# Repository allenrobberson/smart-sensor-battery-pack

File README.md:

# Smart Sensor Battery Pack (18350 / 18650 / 21700 / universal)

A small battery board for a Seeed XIAO microcontroller and an SHTC3 temperature and humidity sensor, for building wireless sensors that run on a single lithium-ion cell. The XIAO plugs into sockets on the front, and the cell sits in a holder on the back.

This is a fork of [FeatureNAB/smart-sensor-battery-pack](https://github.com/FeatureNAB/smart-sensor-battery-pack). It adds two larger battery sizes (18650 and 21700), a **universal board** that takes any of the three holders, a few protection and power improvements, and ready-to-use ESPHome firmware for Home Assistant. All the boards share the same circuit and front-side layout. The full list of changes is under [Changes from the original design](#changes-from-the-original-design).

**Downloads:** each board option (18350, 18650, 21700, universal) comes as one zip on the [Releases page](https://github.com/allenrobberson/smart-sensor-battery-pack/releases). Each zip has the Gerbers, the JLCPCB BOM and placement files, the case STLs, the firmware and a KiCad project that opens on its own.

> **U6 rotation fix (12 November 2026):** placement (CPL) files downloaded before this date have U6 (CSD85301Q2) at 180°; the correct angle is 90°. Use the v1.0 release files. If you already ordered with the old files, ask JLCPCB to rotate U6 to 90° (see [the rotation note](#assembled-by-jlcpcb-bom-and-placement-files)).

The original design, with the build, design theory and assembly, is explained in this video:

## Thank you
A big thank you to **FeatureNAB** for designing this board and sharing it openly, along with the video that explains how and why it works. The charging, protection and sensor-isolation design, the compact layout, and the KiCad project are all their work. This fork only builds on that foundation. If you find this useful, please watch and support the [original video](https://www.youtube.com/watch?v=-wEKOhVZ0NM) and [repository](https://github.com/FeatureNAB/smart-sensor-battery-pack).

## Changes from the original design
**New board sizes**
- **18650 board** (`variants/18650/`): Keystone 1042 holder, 23 x 86.25 mm.
- **21700 board** (`variants/21700/`): Keystone 1121 holder (also fits 20700), 24 x 84.55 mm.
- **Universal board** (`variants/universal/`): one 24 x 86.25 mm board with pads and peg holes for the 1096, 1042 *or* 1121 holder, so one design covers 18350, 18650 and 21700. See [Universal](#universal-18350-18650-and-21700-on-one-board).
- **3D-printable case** (`case/`): a base and lid for every board size, including the universal board, with a USB-C window, sensor vents and wall-mount tabs. See [3D-printable case](#3d-printable-case).
- **Variant generator** (`tools/make_variant.py`): rebuilds the larger boards from the 18350 master after any change, swaps the holder, resizes the outline and checks that the holder's holes clear existing copper.

**Circuit changes (all boards)**

| Part | Original | This fork | Why |
|------|----------|-----------|-----|
| Q2 (new) | — | AO3401A P-MOSFET in the battery + line | Protects everything if the cell is inserted backwards |
| U4 regulator | TPS7A05 (200 mA) | RT9080-33GJ5 (600 mA, 2 µA quiescent) | The ESP32-C6 draws up to 354 mA when Wi-Fi transmits; same footprint and pinout |
| C3 (3.3 V cap) | 2.2 µF | 10 µF | Absorbs Wi-Fi current bursts |
| R2 (charger TS) | 10 kΩ fixed resistor | 10 kΩ NTC thermistor, moved away from the charger | Stops charging when too cold or hot; the fixed resistor disabled this |
| R1 (charge current) | 1.2 kΩ (450 mA) | 18350: unchanged. 18650 and 21700: 910 Ω (about 590 mA). Universal: 1 kΩ (about 540 mA) | Larger cells finish charging inside the charger's 10-hour safety timer |
| U1 (schematic) | XIAO nRF52840 | XIAO ESP32-C6 | Matches the firmware; the sockets are the same |

The 18350 board keeps its original size and front layout; Q2 and the moved thermistor fit in free space in the top-right corner.

**Firmware and Home Assistant (new)**
- **ESPHome config** for the XIAO ESP32-C6 (`firmware/`) with deep sleep, sensor power sequencing, internal I2C pull-ups disabled and pins released before sleep, so the sensor is never powered through its data lines.
- **Home Assistant package** (`homeassistant/`) adding a "stay awake" toggle for over-the-air updates, plus a secrets template.

**Manufacturing files (new)**
- **Gerber zips** for all four boards (18350, 18650, 21700, universal) in `gerbers/`, generated by `tools/make_gerbers.py` and checked for shorts and broken connections.
- **JLCPCB assembly files** (BOM with LCSC part numbers, and placement files) in `assembly/`; the schematics now carry LCSC numbers for the new parts.

**Documentation**
- **I2C note corrected:** the original note said pull-ups were missing. R9 and R10 are already in the design, on the switched sensor rail.
- **Points from the original project's [issue #1](https://github.com/FeatureNAB/smart-sensor-battery-pack/issues/1) ("Missing Pull Up Resistor"):**
  - *Pull-ups on the switched rail (3V_SW) vs. 3V3:* kept on 3V_SW on purpose. Pull-ups on the always-on 3V3 would push current into the SHTC3 through SDA/SCL while its supply is off (phantom powering). On 3V_SW, the pull-ups and the sensor are switched on and off together.
  - *"The sensor has to be powered before the bus starts":* the firmware switches the sensor rail on at boot priority 1200, before I2C sets up (priority 1000), and waits 5 ms so the sensors are ready. No extra YAML is needed.
  - *"Use the internal pull-ups instead":* not used. The ESP32-C6's internal pull-ups are about 45 kΩ, too weak to be reliable, and they would phantom-power the sensor during sleep. They are disabled.
  - *Pull-up current:* none while the bus is idle (I2C is open-drain), and none at all while the rail is off.
  - *Measured 380 µA asleep and a 3.45 s wake:* the firmware now sleeps 2 s after Home Assistant connects instead of staying awake a fixed 20 s, so a typical wake is about 3–6 s and uses roughly a quarter of the energy. See [Sleep current](#sleep-current) for how to measure.
  - *Static IP slower for one tester:* the config now says to measure before relying on a static IP.
  - *Edge.Cuts DRC errors:* the outlines of all three boards here are closed (checked: no open ends).
  - *Larger + / − battery marks:* the holder footprints have small + and − marks on the back silkscreen. Reverse-battery protection (Q2) also protects the board if a cell goes in backwards.
- **README rewritten:** board descriptions, comparison images, setup steps and known limitations.

## Quick start
Here's everything you need to build one, in order:

1. **Pick a board:** 18350 (smallest), 18650 or 21700 (longest runtime), or the universal board if you want to choose the cell later. See [The board designs](#the-board-designs).
2. **Order the board:** upload that board's Gerber zip from [`gerbers/`](gerbers) to JLCPCB. Optionally add assembly with the matching BOM and placement files from [`assembly/`](assembly); see [Ordering boards](#ordering-boards-gerber-files).
3. **Buy the parts that aren't on the board order:**
   - The **battery holder** for your size, from DigiKey (see [Battery holders](#battery-holders)).
   - A **Seeed XIAO ESP32-C6** ([product wiki](https://wiki.seeedstudio.com/xiao_esp32c6_getting_started)).
   - A **lithium-ion cell** (see [Batteries](#batteries)).
4. **Solder the holder, then check the board** before inserting a cell (see [Assembly and first power-up](#assembly-and-first-power-up)).
5. **Flash the firmware and add the sensor to Home Assistant** (see [Firmware](#firmware-esphome-xiao-esp32-c6)).
6. **Optionally plug in a second sensor** (see [Adding other sensors](#adding-other-sensors)).

## What the board does
- **Microcontroller:** made for a Seeed **XIAO ESP32-C6**. The board uses D2 (GPIO2) for battery voltage, D4/D5 (GPIO22/23) for I2C and D10 (GPIO18) to switch the sensor power.
- **Charging:** a BQ21040 charges the cell from the XIAO's USB 5 V, and an LED shows charge status. R1 sets the charge current: 450 mA on the 18350 board and about 590 mA on the 18650 and 21700 boards, so a full charge fits inside the charger's 10-hour safety timer.
- **Battery temperature:** a 10 kΩ NTC thermistor (R2, Murata NCP15XH103F03RC) on the charger's TS pin stops charging when the board is too cold or too hot for lithium-ion. It sits in the corner furthest from the charger so the charger's own heat doesn't trip it.
- **Reverse-battery protection:** a P-channel MOSFET (Q2, AO3401A) in series with the cell's + terminal, with its gate on the cell's − terminal. A correctly inserted cell turns it fully on in both directions, for charging and discharging. A reversed cell leaves it off, and its body diode blocks the current.
- **Cell protection:** a BQ29700 protector with a CSD85301Q2 dual MOSFET guards against over-charge, over-discharge and over-current.
- **Power:** an RT9080-33GJ5 regulator (600 mA, 2 µA quiescent current) supplies 3.3 V to the XIAO. That covers the ESP32-C6's Wi-Fi transmit peaks (up to 354 mA at full power) with headroom, and a 10 µF capacitor (C3) on 3.3 V absorbs the bursts.
- **Battery monitoring:** a 5.1 MΩ / 5.1 MΩ divider brings the battery voltage to a XIAO analog pin (BATT_SENSE) and draws about 0.4 µA.
- **Switched sensor power:** a P-channel MOSFET (Q1, AO3401A) lets the XIAO turn the sensor rail (3V_SW) off between readings. The I2C pull-ups (R9, R10) are on that rail too, so nothing on the sensor side draws current while the XIAO sleeps.
- **Sensor:** an SHTC3 sits on a slotted tab at the bottom edge, thermally isolated from the rest of the board, with an extra socket for a plug-in I2C sensor.

## The board designs
All the boards share the same schematic and the same front-side parts and routing. Only the holder on the back, the board outline and the two battery traces change. The extra length is added at the BAT+ end, so the sensor tab stays where it is.

| Cell | Holder (back side) | Holder mounting | Board size | KiCad project |
|------|--------------------|-----------------|------------|---------------|
| 18350 | Keystone 1096 | Surface mount | 23 x 56 mm | repository root (original design) |
| 18650 | Keystone 1042 | Surface mount | 23 x 86.25 mm | `variants/18650/` |
| 21700 | Keystone 1121 (fits 20700 and 21700) | Through-hole solder lugs | 24 x 84.55 mm | `variants/21700/` |
| **Universal** | Keystone 1096, 1042 **or** 1121 | SMD pads + lug holes for all three | 24 x 86.25 mm | `variants/universal/` |

### 18350
The original, most compact design. The Keystone 1096 holder covers the whole back of the board.

### 18650
The same board stretched to 86.25 mm for a Keystone 1042 holder. The holder's locating holes are placed to clear all existing copper. The BAT- pad overhangs the bottom edge by 0.25 mm, which DRC will flag; the original board overhangs its BAT+ pad by 0.95 mm in the same way.

### 21700
Uses a Keystone 1121 holder. The holder is 23.06 mm wide, so the board is 1 mm wider than the original, with the extra width on the right so the sensor tab is unchanged. The holder's solder lugs go through the board and are soldered from the front.

The footprint was drawn from Keystone drawing 1121 rev A. The lug holes are drilled 1.7 mm instead of the drawing's 1.32 mm, because the drawing gives the lug pin itself as 1.57 mm. Check a lug against the hole before ordering.

### Universal (18350, 18650 and 21700 on one board)
One board that takes any of the three holders, so you can order a single design and choose the cell later. It is the 21700 board lengthened to 86.25 mm (the 1042's length), 24 mm wide.

- **BAT- end (bottom):** one larger SMD pad covers both the 1096 and the 1042 contact, with the 1121's plated lug hole in the middle of it. All three holders' − contacts land here.
- **BAT+ end (top):** the + pad for the 1042 (18650) sits at the top edge, with the 1121's (21700) lug hole inside it. A second + pad for the 1096 (18350) sits 30.7 mm further down. The two are joined by the BAT+ trace on the back, under solder mask, so there is no long strip of bare battery copper. The back silkscreen shows which + pad belongs to which cell (`18650 21700` and `18350`), plus large + and − marks.
- **Locating holes:** every holder's pegs have a hole. Where two holders' pegs overlap, the holes are merged into slots: one small and one large slot on the left, and one large slot on the right. All holes keep at least 0.3 mm from copper.
- **Charge current:** R1 is **1 kΩ (about 540 mA)**, LCSC C11702, a basic part. That's under 0.5C for a 1100 mAh 18350 and still charges a 4500 mAh 21700 inside the charger's 10-hour safety timer. With a 5000 mAh cell charged from empty, the timer can stop the charge just before it finishes; unplugging and replugging USB restarts it. For an 18650/21700-only build, you can fit 910 Ω (C44933) instead.
- **Soldering the holder:** for the 1096 or 1042, solder the contacts to the pads; the small lug holes under them just fill with solder. For the 1121, solder its lugs from the front as on the 21700 board. Only fit one holder.

The front side, parts and routing are the same as the other three boards, so the same firmware and BOM apply. The only BOM difference is R1. The board and its files were made by `tools/make_universal.py`.

**What has been checked:** the Gerbers have no shorts or broken nets; every hole and slot keeps at least 0.3 mm from other-net copper; no copper is within 0.25 mm of the board edge; JLCPCB accepted the files, matched all 19 parts and showed the slots correctly; and every part's rotation was checked in JLCPCB's placement preview (pin-1 marks and leads on pads). **Not yet checked:** a KiCad DRC run (open `variants/universal/` in KiCad, press B to refill zones, then run DRC) and a physical test-fit of each holder. Check the peg slots against a real holder before ordering in quantity.

## 3D-printable case
A two-part case (base + lid) for every board, in [`case/stl/`](case/stl). Details and print settings are in [`case/README.md`](case/README.md).

| Board | Print |
|---|---|
| 18350 | [`case-18350-base.stl`](case/stl/case-18350-base.stl) + [`case-18350-lid.stl`](case/stl/case-18350-lid.stl) |
| 18650 | [`case-18650-base.stl`](case/stl/case-18650-base.stl) + [`case-18650-lid.stl`](case/stl/case-18650-lid.stl) |
| 21700 | [`case-21700-base.stl`](case/stl/case-21700-base.stl) + [`case-21700-lid.stl`](case/stl/case-21700-lid.stl) |
| Universal | the base for the holder you fitted ([`18350`](case/stl/case-universal-18350-base.stl), [`18650`](case/stl/case-universal-18650-base.stl) or [`21700`](case/stl/case-universal-21700-base.stl)) + [`case-universal-lid.stl`](case/stl/case-universal-lid.stl) |

More views of each case (exploded, base, lid from below, assembled) and cut-away fit checks are in [`case/images/`](case/images).

- **Base:** the board drops in battery-side down and rests on ribs under the holder's end walls.
- **Lid:** clicks onto a lip on the base; small fingers stop just above the board's edges so it can't move.
- **USB-C window:** lined up with the XIAO's USB-C port, so you can charge and flash without opening the case.
- **Vents** next to the SHTC3 sensor tab and across the roof, so the sensor reads room air; **wall-mount tabs** on both ends.
- **Checked:** the generator checks every case against the board, holder, cell, every part, the XIAO and the USB-C plug path, and checks that the STLs are watertight. The case hasn't been test-printed yet. If your sockets or headers are a different height, change the values at the top of [`tools/make_case.py`](tools/make_case.py) and run it again.

## Ordering boards (Gerber files)
Ready-to-upload Gerber zips for all four boards are in [`gerbers/`](gerbers):

| Board | File | Size |
|-------|------|------|
| 18350 | [`gerbers/SSB-18350-gerbers.zip`](gerbers/SSB-18350-gerbers.zip) | 23 x 56 mm |
| 18650 | [`gerbers/SSB-18650-gerbers.zip`](gerbers/SSB-18650-gerbers.zip) | 23 x 86.25 mm |
| 21700 | [`gerbers/SSB-21700-gerbers.zip`](gerbers/SSB-21700-gerbers.zip) | 24 x 84.55 mm |
| Universal | [`gerbers/SSB-UNIVERSAL-gerbers.zip`](gerbers/SSB-UNIVERSAL-gerbers.zip) | 24 x 86.25 mm |

**To order at JLCPCB:** upload a zip on the quote page and keep the defaults: 2 layers, 1.6 mm FR-4, 1 oz copper. Choose any solder-mask colour. If you want JLCPCB to assemble the parts, pick **LeadFree HASL** so the cheaper Economic assembly is allowed (see [Tested JLCPCB order settings](#tested-jlcpcb-order-settings-november-2026)). Each zip holds both copper layers, solder mask, paste, silkscreen, the board outline, and plated and non-plated drill files.

*Copper as written to the Gerbers (white = copper), front and back for 18350, 18650 and 21700. The back views are mirrored as if the board were flipped over.*

### Assembled by JLCPCB (BOM and placement files)
To have JLCPCB solder the parts, choose **PCB Assembly** (top side) on the quote page, then upload the BOM and placement (CPL) files for the same board from [`assembly/`](assembly):

| Board | BOM | Placement |
|-------|-----|-----------|
| 18350 | [`SSB-18350-BOM.csv`](assembly/SSB-18350-BOM.csv) | [`SSB-18350-CPL.csv`](assembly/SSB-18350-CPL.csv) |
| 18650 | [`SSB-18650-BOM.csv`](assembly/SSB-18650-BOM.csv) | [`SSB-18650-CPL.csv`](assembly/SSB-18650-CPL.csv) |
| 21700 | [`SSB-21700-BOM.csv`](assembly/SSB-21700-BOM.csv) | [`SSB-21700-CPL.csv`](assembly/SSB-21700-CPL.csv) |
| Universal | [`SSB-UNIVERSAL-BOM.csv`](assembly/SSB-UNIVERSAL-BOM.csv) | [`SSB-UNIVERSAL-CPL.csv`](assembly/SSB-UNIVERSAL-CPL.csv) |

Every part except the battery holder uses a JLCPCB/LCSC part number:

| Part | Designator | LCSC # |
|------|-----------|--------|
| Charger BQ21040DBVR | U2 | C202311 |
| Protector BQ29700DSER | U5 | C183096 |
| Dual MOSFET CSD85301Q2 | U6 | C544396 |
| Regulator RT9080-33GJ5 | U4 | C841192 |
| P-MOSFET AO3401A | Q1, Q2 | C15127 |
| SHTC3 sensor | U7 | C194656 |
| 10 kΩ NTC (Murata NCP15XH103F03RC) | R2 | C77131 |
| 10 µF 0603 | C3 | C19702 (basic part) |
| 2.2 µF 0603 | C1, C2 | C23630 (basic part) |
| 100 nF 0402 | C4, C5, C6 | C1525 |
| Charge-current resistor | R1 | 1.2 kΩ C25862 (18350), 910 Ω C44933 (18650, 21700) |
| Other 0402 resistors, LED | R3–R12, D1 | see the BOM files |
| XIAO sockets 1x7 / 1x5 SMD | J1, J2, J3 / J5 | C42379199 / C42379198 |

Things to know before ordering assembly:
- **Battery holder:** BT1 is not in the BOM, so buy it separately and solder it yourself (see [Battery holders](#battery-holders) below).
- **Extended parts:** most of the ICs are JLCPCB "extended" parts, which carry a small one-time loading fee each. Stock changes, so the quote page will flag anything that has run out.
- **Rotations are already corrected:** the CPL files include JLCPCB's zero-angle offsets for the sockets, SOT-23, SOT-23-5, SOT-23-6, SHTC3 and CSD85301Q2 parts (see `ROTATION_FIX` in `tools/make_jlc_bom.py`). Every part was checked in JLCPCB's placement preview: each IC's pin-1 marker sits at the board's pin-1 mark and its leads on the pads. All four boards share identical front-side pads and placement data, so the check covers all of them. **U6 (CSD85301Q2) needs 90°, not 180°:** JLCPCB's library footprint for C544396 has the pins in rows with pin 1 bottom-left, while the KiCad footprint has them in columns. The first CPL files (used for the November 2026 order of the 18350/18650/21700 boards) had U6 at 180°, which turns the part 90° on its pads. This was fixed on 12 November 2026; if you downloaded the assembly files before then, download them again. **If you already placed an order with the old CPL file,** message JLCPCB (through the order's File Review or support chat) before assembly and ask them to place U6 (CSD85301Q2, C544396) at 90° so that pin 1 sits at the silkscreen dot. They can correct the rotation on an order that is still in review.
- **The XIAO:** it plugs into the sockets and isn't part of the order.

#### Tested JLCPCB order settings (November 2026)
The 18350, 18650 and 21700 Gerbers and BOMs are exactly the ones uploaded for a real order of those three boards. Their CPL (placement) files have since had one fix: U6 is now at 90° instead of 180° (see the rotation note above). The universal board's files were uploaded with the same settings and quoted at **$73.82** for 5 assembled boards ($5.10 PCB + $68.72 assembly, including $0.91 nitrogen reflow); all 19 parts matched and were in stock, and JLCPCB's preview showed its slotted holes correctly. These settings went through without errors:

| Setting | Value | Why |
|---------|-------|-----|
| Surface finish | **LeadFree HASL** | Economic PCBA does not accept OSP. Lead-free HASL costs about $1.10 more, but it unlocks the much cheaper assembly tier |
| PCBA type | **Economic** | Setup fee about $8 instead of about $26, a $1.55 stencil instead of $8.27, and no per-feeder loading fees (only a ~$3 fee per extended part) |
| PCB qty / PCBA qty | 5 / 5 | Economic PCBA allows 2 to 50 assembled boards |
| Assembly side | Top | BT1 on the back is soldered by hand |
| Tooling holes | Added by JLCPCB | Default |
| Product description | Sensor\Controller\Precision Instrument / Temperature Sensor | Needed for customs |
| Assembly remark | (optional) "Please confirm pin 1 of U6 (CSD85301Q2, C544396) is at the silkscreen dot, bottom-right of U6." | A second check on the one part whose rotation had to be corrected. The **Assembly Remark** box doesn't always appear; if it's missing, raise it during **File Review** in your order history. Don't use the 200-character **PCB Remark** box, which goes to the board factory, not assembly. |

Quoted price for 5 assembled boards, before shipping and coupons:

| Board | PCB | Assembly (Economic) | Total |
|-------|-----|---------------------|-------|
| 18350 | $5.10 | $68.74 | **$73.84** |
| 18650 | $5.10 | $71.84 | **$76.94** |
| 21700 | $5.10 | $71.84 | **$76.94** |

Assembly breakdown (Economic PCBA, 5 boards):

| Item | 18350 | 18650 | 21700 |
|------|-------|-------|-------|
| Setup fee | $8.24 | $8.24 | $8.24 |
| Stencil | $1.55 | $1.55 | $1.55 |
| Components (19 BOM lines) | $26.09 | $26.10 | $26.10 |
| Extended components fee | $30.90 | $33.99 | $33.99 |
| SMT assembly | $1.05 | $1.05 | $1.05 |
| Nitrogen reflow | $0.91 | $0.91 | $0.91 |
| **Assembly total** | **$68.74** | **$71.84** | **$71.84** |
| PCB (5 boards, lead-free HASL) | $5.10 | $5.10 | $5.10 |
| **Per order** | **$73.84** | **$76.94** | **$76.94** |
| **Per assembled board** | **$14.77** | **$15.39** | **$15.39** |

Universal board (quoted the same way): $5.10 PCB + $68.72 assembly = **$73.82** for 5 assembled boards ($14.76 each), the same extended-part fees as the 18350.

The 18350 has one fewer extended part than the other two (its R1, C25862, is a basic part), so its fee is lower.

All three boards in one checkout (15 assembled boards), as actually ordered and shipped to the US in November 2026:

| | Cost |
|---|---|
| Merchandise (3 × PCB + PCBA) | $227.72 |
| Shipping (the cart page had estimated $31.69 for UPS Express Saver) | $64.13 |
| US customs duties and taxes | $79.73 |
| Duty and tax disbursement fee | $4.44 |
| **Order total** | **$376.02** (about $25 per assembled board) |

**Budget for more than the cart shows.** The cart's shipping estimate is only a starting point: the shipping charge depends on the method you choose at checkout. US import duties and taxes on the assembled boards came to about 35% of the merchandise total, and JLCPCB charges them at checkout (DDP). Coupons (below) come off the total. Ordering fewer board sizes lowers every line, since each design is a separate PCB + PCBA order.

Not included: the battery holder (BT1, bought separately, see [Battery holders](#battery-holders)), the XIAO ESP32-C6 and the battery.

**Coupons:** JLCPCB uses account coupons rather than codes, and you choose them in the payment step of checkout. New accounts get New User SMT ($10), PCB ($6) and Shipping ($10) coupons, and the [coupon center](https://jlcpcb.com/coupon-center) has more (for example, "PCBA Special Offer" $9/$6). Checking out in the **JLCONE desktop app** unlocks a "JLCONE PCBA $20" coupon for assembly orders over $100, which beats the $10 one for a three-board order. JLCPCB's terms allow one coupon per order, so the checkout page has the final say. Check out all three boards together: separate orders each pay their own shipping (about $27), which costs more than the extra coupons save.

For comparison, the same 18350 order as *Standard* PCBA on OSP came to $96.33.

**Ways to cut the cost further:**
- **Order 2 assembled boards instead of 5.** Most of the assembly cost is per-order fees (setup, extended-part fees), so 2 boards cost only a little less than 5, but the total is still lower if you only need one or two.
- **Order one or two sizes, not all three.** Each design pays its own setup and extended-part fees.
- **Solder the XIAO sockets yourself.** J1–J3 and J5 (C42379199, C42379198) cost about $5.65 in parts per 5-board order, plus two extended-part fees (about $6). Untick them on the BOM page and solder ordinary 2.54 mm female headers.
- **Drop the status LED.** D1 (and its resistor R8) are optional. Unticking D1 saves one extended-part fee.
- **Basic parts were preferred** where they did not change the circuit: R7 (100 kΩ) uses basic part C25741.
- **Order only the universal board** if you haven't decided on a cell size: one design covers all three holders, so you pay one set of setup and extended-part fees.

**Part changes made while ordering:**
- **R1 on the 18650/21700:** C4129882 (910 Ω, 5%) was out of stock, so R1 is now Uniroyal 0402WGF9100TCE, **C44933** (910 Ω, 1%, about 228k in stock). The value and charge current (about 590 mA) are unchanged.
- **R7, all boards:** now C25741 (basic, 1%) instead of C25530 (extended, 5%). Same 100 kΩ value.

### Battery holders
**Note:** the battery holder is the one part JLCPCB does not assemble. It isn't in the BOM, because JLCPCB doesn't reliably stock these Keystone holders and they mount on the back of the board, which would need a second, more expensive assembly side. Order the holder for your board size and solder it yourself after the boards arrive.

Each board is laid out for one specific Keystone holder, and only that part fits its pads and locating holes:

| Board | Holder | Mounting | DigiKey |
|-------|--------|----------|-----|
| 18350 | Keystone **1096** | Surface mount (tabs soldered on the back) | [36-1096-ND](https://www.digikey.com/en/products/detail/keystone-electronics/1096/5057788) |
| 18650 | Keystone **1042** | Surface mount (tabs soldered on the back) | [36-1042-ND](https://www.digikey.com/en/products/detail/keystone-electronics/1042/2745668) |
| 21700 | Keystone **1121** (fits 20700 and 21700) | Through-hole lugs (soldered from the front) | [36-1121-ND](https://www.digikey.com/en/products/detail/keystone-electronics/1121/12751670) |

**Soldering tips**
- **1096 and 1042:** the holder sits on the back. Tack one tab, check the holder is flat with its locating pegs in the holes, then solder the other tab. The tabs are large, so use a hot iron (about 350 °C) and plenty of flux.
- **1121:** push the lugs and pegs through from the back, then solder the two lugs on the front.
- **Polarity:** check it before inserting a cell. The + end of the holder must match the + mark on the board (the BAT+ end, away from the sensor tab). Q2 protects the board if a cell goes in backwards, but double-check anyway.

The files come from [`tools/make_jlc_bom.py`](tools/make_jlc_bom.py), which reads the *LCSC Part no.* field from each schematic and the positions from the board, in the same coordinates as the Gerbers.

**How these were made:** KiCad was not available, so the files were generated by [`tools/make_gerbers.py`](tools/make_gerbers.py) directly from the `.kicad_pcb` files. It fills the copper pours itself: ground copper everywhere, a 0.5 mm gap around every other net and the board edge, and no copper in the keep-out areas. Every copper layer was then rasterized at 0.02 mm and checked automatically. There are no shorts between nets, no broken connections, and every pad, via and trace sits on copper. The check was itself tested by deliberately breaking a trace, which it caught. The differences from a KiCad export are:
- **Solid ground connections:** pads and vias on the ground pour are joined solidly rather than through thermal-relief spokes. Ground pads take a little longer to heat when hand-soldering.
- **Square pad corners:** rounded-rectangle pads are drawn as plain rectangles.
- **Outline-only silkscreen:** part outlines are drawn, but there's no text (reference designators and the logo). Use the board images above while assembling.

If you have KiCad 9, the safer route is still to open each project, press **B** to refill the zones, run DRC, and plot your own Gerbers. To regenerate these files after a design change, run:
```
python3 tools/make_gerbers.py <board.kicad_pcb> <output_dir> --name <prefix>
```

## Before ordering boards
The design changes in this fork (reverse-battery transistor, NTC, new regulator, larger boards) were made by script. They were checked with the clearance, connectivity and Gerber checks described above, but not with KiCad's own DRC, and no board has been built yet. Order a small batch first.

### Known limitations
- **Cell temperature is measured on the board, not on the cell.** The thermistor sits on the front, above the cell, so it reads board temperature. Charging can pause on a hot day once the board passes about 45 °C.
- **A completely flat cell (near 0 V) won't charge.** Q2 needs a couple of volts across the cell to turn on. Cells that low shouldn't be recovered anyway.
- **USB plugged in with a nearly empty cell.** When the XIAO runs from USB, its own regulator also drives 3.3 V. If the cell is below about 3.0 V at that moment, the RT9080's output sits slightly above its input, past its 0.3 V reverse rating. The original design had the same behaviour; it lasts only until the cell charges past 3 V.

## Connectors and pinout
The XIAO plugs into J1 and J2. J3 and J5 are for an optional plug-in sensor.

| Socket | Pin 1 | Pin 2 | Pin 3 | Pin 4 | Pin 5 | Pin 6 | Pin 7 |
|--------|-------|-------|-------|-------|-------|-------|-------|
| **J1** (XIAO left row) | D0 – free | D1 – free | D2 – BATT_SENSE | D3 – free | D4 – SDA | D5 – SCL | D6 – free |
| **J2** (XIAO right row) | D7 – free | D8 – free | D9 – free | D10 – sensor power (Q1) | 3V3 | GND | 5V (USB) |
| **J3** (sensor socket, top edge) | 3V3 switched | not connected | GND | SCL | SDA | not connected | not connected |
| **J5** (sensor socket, middle) | SDA | SCL | GND | not connected | 3V3 switched |  |  |

- **Switched 3.3 V:** this rail on J3 and J5 is the sensor rail controlled by Q1. It's only powered while the firmware holds D10 (GPIO18) low, so a plug-in sensor is switched off during deep sleep, just like the onboard SHTC3.
- **J3's pin order** (power, unused, GND, SCL, SDA) is the common breakout header order *VIN, 3Vo, GND, SCL, SDA*, so many 5-pin breakouts plug straight in. Always check the header order printed on your breakout first.
- **Free XIAO pins:** D0, D1, D3, D6, D7, D8 and D9 aren't connected to anything on the board, so you can use them for your own additions.

## Batteries
- **Cell type:** use a single **3.7 V lithium-ion cell** of the size your board is built for (18350, 18650, or 20700/21700; on the universal board, the size of the holder you fitted). The board has its own protection (BQ29700) and reverse-battery protection (Q2), so unprotected cells are fine.
- **Cell length:** protected cells are a few millimetres longer and may not fit the holder.
- **Cell source:** buy from a reputable cell manufacturer or a known battery retailer. Avoid unbranded cells with inflated capacity ratings.
- **Charge time:** about 3 hours for a typical 18350, 6–8 hours for an 18650 and up to about 9 hours for a 5000 mAh 21700. The charger's 10-hour safety timer covers all of these.
- **Polarity:** match the cell's + end to the + mark on the holder. Q2 protects the board if a cell goes in backwards, but the cell won't charge or run the board until it's turned around.

## Assembly and first power-up
1. **Solder the board:** solder the battery holder, and anything else you didn't have assembled. The [BOM files](assembly) list every part with its LCSC number, so you can also order them from LCSC and hand-solder.
2. **Check before inserting a cell:** use a multimeter to check there's no short between the holder's + and − pads, or between 3V3 and GND on J2.
3. **First power on USB only:** insert the XIAO, but no cell yet, and plug USB into the XIAO. The charge LED may flicker, because the charger is looking for a battery; that's normal.
4. **Flash the firmware** over USB (see [Firmware](#firmware-esphome-xiao-esp32-c6)).
5. **Insert the cell:** with USB still connected, the charge LED should light while the cell charges and turn off when it's full.
6. **Check the readings:** with USB unplugged, the node should wake, report temperature, humidity and battery voltage, and go back to sleep. The battery voltage in Home Assistant should be within about 0.1 V of a multimeter reading across the cell.

## Adding other sensors
Any 3.3 V I2C sensor breakout can plug into J3 or J5. It shares the bus with the onboard SHTC3 (address 0x70), so its I2C address must not be 0x70. The sensors below all have ESPHome support (platform names checked against the ESPHome docs; each name links to its page), and suit a battery-powered node:

| Sensor | Measures | ESPHome platform | Fit for this board |
|--------|----------|------------------|-------------------|
| **SHT40 / SHT45** | Temperature, humidity (more accurate than the SHTC3) | [`sht4x`](https://esphome.io/components/sensor/sht4x.html) | Excellent: fast, microamp current |
| **BME280** | Temperature, humidity, air pressure | [`bme280_i2c`](https://esphome.io/components/sensor/bme280.html) | Excellent |
| **BMP280** | Temperature, air pressure | [`bmp280_i2c`](https://esphome.io/components/sensor/bmp280.html) | Excellent |
| **AHT20** | Temperature, humidity | [`aht10`](https://esphome.io/components/sensor/aht10.html) with `variant: AHT20` | Excellent, low cost |
| **BH1750** | Light level (lux) | [`bh1750`](https://esphome.io/components/sensor/bh1750.html) | Excellent |
| **VEML7700** | Light level, wide range | [`veml7700`](https://esphome.io/components/sensor/veml7700.html) | Excellent |
| **TSL2591** | Light level, high dynamic range | [`tsl2591`](https://esphome.io/components/sensor/tsl2591.html) | Good |
| **LTR390** | UV index and light | [`ltr390`](https://esphome.io/components/sensor/ltr390.html) | Good |
| **SCD40 / SCD41** | CO₂ (true NDIR), temperature, humidity | [`scd4x`](https://esphome.io/components/sensor/scd4x.html) | Works, but set `measurement_mode: single_shot` (each reading takes about 5 s) and a longer `report_delay` (about 7 s). CO₂ sensors draw much more current than the others, so battery life drops noticeably |
| **BME680 / BME688** | Temperature, humidity, pressure, gas (VOC) | [`bme680`](https://esphome.io/components/sensor/bme680.html) | Temperature, humidity and pressure work well. The gas reading needs the sensor powered continuously to stabilize, so it's unreliable when the sensor is switched off between readings |
| **SGP40 / SGP41, ENS160** | Air quality (VOC/NOx) | [`sgp4x`](https://esphome.io/components/sensor/sgp4x.html), [`ens160_i2c`](https://esphome.io/components/sensor/ens160.html) | Not recommended: they need continuous power and a warm-up period, which defeats deep sleep |

**Tips:**
- **Pull-up resistors:** breakouts with their own pull-ups are fine; they sit in parallel with R9 and R10. Breakouts with a power LED waste battery, so cut or remove the LED if you can.
- **5 V-only sensors** such as particulate sensors and most PMS-series modules won't work. The sockets supply 3.3 V only.
- **Config example:** add the sensor to the ESPHome config next to the SHTC3. For example, an SHT40:
  ```yaml
  sensor:
    - platform: sht4x
      temperature:
        name: Temperature (SHT40)
      humidity:
        name: Humidity (SHT40)
      update_interval: 5s
  ```

## Firmware (ESPHome, XIAO ESP32-C6)
A complete ESPHome config is in [`firmware/smart-sensor-xiao-esp32c6.yaml`](firmware/smart-sensor-xiao-esp32c6.yaml). It does the following:

- **Deep sleep:** the node wakes, reads temperature, humidity and battery voltage, reports them, and sleeps again. By default it goes back to sleep 2 s after Home Assistant connects (usually 3–6 s awake in total), sleeps 5 minutes, and never stays awake longer than 20 s; change `report_delay`, `sleep_time` and `awake_time` at the top.
- **Sensor power sequencing:** GPIO18 is driven low at boot priority 1200, before I2C starts (priority 1000), so the sensor and its pull-ups are powered when the bus is set up.
- **No phantom powering:** the ESP32-C6's internal I2C pull-ups are turned off. Just before deep sleep, SDA, SCL and GPIO18 are set to high-impedance with no pulls; R7 then switches the sensor rail off. Nothing can drive the sensor through its data pins while it is unpowered.
- **Lower radio power:** Wi-Fi uses `fast_connect`, light power-save and 15 dB transmit power to shorten and cheapen each wake-up. The regulator handles full power if you need the range.
- **Antenna:** the XIAO's RF switch is enabled with its built-in antenna selected. Set GPIO14 high in the boot lambda to use the U.FL connector.

- **Stay-awake switch:** while `input_boolean.smart_sensor_stay_awake` is on in Home Assistant, the node skips deep sleep so you can update it over the air or watch its logs. It picks the change up the next time it wakes.

### Setting it up in Home Assistant
1. **Install ESPHome:** add the ESPHome Device Builder add-on in Home Assistant (Settings → Add-ons), or use the `esphome` command line on your computer.
2. **Add the secrets:** copy [`firmware/secrets.yaml.example`](firmware/secrets.yaml.example) to `secrets.yaml` and fill in your Wi-Fi details, an API encryption key, an OTA password and a fallback-hotspot password. In the Device Builder, open **Secrets** (top right) and paste the same keys there. `secrets.yaml` is ignored by git, so it won't be committed.
3. **Add the device:** in the Device Builder choose **New device**, skip the wizard, and paste the contents of `smart-sensor-xiao-esp32c6.yaml` into the new device's file. You can change `name`, `sleep_time`, `report_delay` and `awake_time` at the top (see [Adjusting the wake and sleep timing](#adjusting-the-wake-and-sleep-timing)).
4. **First flash over USB:** plug the XIAO into your computer and choose **Install → Plug into this computer** (or run `esphome run smart-sensor-xiao-esp32c6.yaml`). Later updates can go over Wi-Fi.
5. **Add the device to Home Assistant:** wake the sensor (press the XIAO's reset button, or turn on the stay-awake toggle from step 6 first) so it is online, then:
   - **If it's discovered:** go to **Settings → Devices & services**. A "Discovered: smart-sensor" card appears; click **Add**, enter the API encryption key from your `secrets.yaml`, and click **Submit**.
   - **If it isn't discovered:** go to **Settings → Devices & services → Add integration**, search for **ESPHome**, enter `smart-sensor.local` (or the sensor's IP address) as the host with port `6053`, then enter the API encryption key.
   - **Pick an area:** choose where the sensor lives (for example "Bedroom") and click **Finish**.
6. **Add the stay-awake toggle:** copy [`homeassistant/smart_sensor_package.yaml`](homeassistant/smart_sensor_package.yaml) to `<config>/packages/` and add this to `configuration.yaml`, then restart Home Assistant:
   ```yaml
   homeassistant:
     packages:
       smart_sensor: !include packages/smart_sensor_package.yaml
   ```
   To update the firmware later, turn the toggle on, wait for the sensor's next wake-up, install the update, then turn the toggle off.

The node appears with **Temperature**, **Humidity**, **Battery voltage** and **Battery level** entities. Because the config uses deep sleep, ESPHome tells Home Assistant it is a sleeping device, so Home Assistant keeps the last reading between wake-ups instead of marking the sensor unavailable.

### Adjusting the wake and sleep timing

#### How often the sensor wakes up (`sleep_time`)
`sleep_time` sets the time between readings. It is the first thing to change if you want more frequent readings or a longer-lasting battery.

1. **Open the config.** In Home Assistant go to **Settings → Add-ons → ESPHome Device Builder**, then click **Edit** on your Smart Sensor. If you use ESPHome on a computer, open `smart-sensor-xiao-esp32c6.yaml` instead.
2. **Change `sleep_time`** in the `substitutions:` block at the top:

   ```yaml
   substitutions:
     sleep_time: 15min    # wake up and send a reading every 15 minutes
   ```

   Use a number followed by a unit: `s` (seconds), `min` (minutes) or `h` (hours), for example `30s`, `5min`, `15min`, `1h`, `12h`, `24h`. The default is `5min`.
3. **Keep the node awake so it can take the update.** A sleeping node can't receive new firmware. In Home Assistant, turn on the **Smart Sensor stay awake** toggle (`input_boolean.smart_sensor_stay_awake`, from `homeassistant/smart_sensor_package.yaml`), then wait for the node's next wake-up. Its status turns online in the ESPHome dashboard.
4. **Install it.** Click **Save**, then **Install → Wirelessly**. The node restarts with the new interval.
5. **Turn the stay-awake toggle off again.** The node goes back to its normal cycle on its next wake.

The time between readings is `sleep_time` plus the few seconds the node is awake, so `5min` gives a reading roughly every 5 minutes and 5 seconds.

**How the interval affects battery life (rough estimate):**

| `sleep_time` | 18350 (~1100 mAh) | 18650 (~3000 mAh) | 21700 (~4500 mAh) |
|---|---|---|---|
| `1min` | about 1 week | about 3 weeks | about 1 month |
| `5min` (default) | about 1 month | about 3 months | about 5 months |
| `15min` | about 3 months | about 9 months | over a year |
| `30min` | about 6 months | over a year | over a year |
| `1h` | about 11 months | over a year | over a year |
| `12h` | about 3 years* | several years* | several years* |
| `24h` | about 3–4 years* | several years* | several years* |

These figures assume each wake lasts about 5 s at an average of about 68 mA (in line with a tester's PPK2 measurements on the original board, see [Sleep current](#sleep-current)) and about 25 µA while asleep, using 90% of the cell's capacity. Weak Wi-Fi, a slow plug-in sensor, a longer `report_delay` and cold temperatures all shorten battery life. Beyond about a year, the cell's own self-discharge starts to matter more than the board.

\* At 12- and 24-hour intervals, the wake-ups barely matter. Battery life is set by the ~25 µA sleep current and the cell's own self-discharge (typically 1–3% a month), so these figures are rough; check the battery level in Home Assistant now and then and recharge at least once a year. Use `sleep_time: 12h` or `24h` (ESPHome also accepts `720min` or `1440min`). For readings this far apart, a 1-hour reading is usually more useful for temperature and humidity; 12–24 hours suits slow-changing things such as a battery check or a storage-room log.

Suggested intervals: 5–15 minutes for temperature and humidity, 15–60 minutes for soil moisture, and 2–5 minutes for CO₂ in a busy room.

#### How long it stays awake
Each cycle, the node wakes, connects to Wi-Fi and Home Assistant, sends its readings, and goes back to sleep. Three values at the top of `smart-sensor-xiao-esp32c6.yaml` control this:

```yaml
substitutions:
  awake_time: 20s     # safety limit: longest the node stays awake each cycle
  sleep_time: 5min    # how long it sleeps between cycles
  report_delay: 2s    # after Home Assistant connects, wait this long, then sleep
```

**How a cycle ends:** the sensors take their first reading within a couple of seconds of boot, while Wi-Fi is still connecting. When Home Assistant connects, it receives those readings and the state of the stay-awake toggle. `report_delay` later the node sleeps, so a typical wake lasts about 3–6 s. `awake_time` only matters when Wi-Fi or Home Assistant can't be reached: the node then gives up and sleeps after 20 s instead of draining the battery.

**When a sensor needs more time:** a reading only gets sent if it finishes before the node sleeps. If a sensor shows up as unknown or never updates:

1. **Raise `report_delay`** to cover the sensor's measurement time. For example, an SCD40/41 in `single_shot` mode takes about 5 s per reading, so use `report_delay: 7s`.
2. **Raise `awake_time` too** if connection time + `report_delay` comes close to it. Rough rule: connection time (about 5–10 s) + `report_delay` + 5 s of margin.
3. **Make sure the sensor reads during that window.** Its `update_interval` must be shorter than the time the node is awake; the provided config uses `5s`. For a slow sensor, set its `update_interval` to at least its measurement time (for example `10s` for an SCD4x).
4. **Sensors that need a warm-up after power-on:** the sensor rail switches on at the very start of boot (5 ms before I2C starts), so most of the warm-up overlaps with the Wi-Fi connection. If a sensor needs longer, add the extra time to `report_delay`. Sensors that need minutes of warm-up (gas/VOC sensors) won't settle in a short wake window at all; see [Adding other sensors](#adding-other-sensors).

**Sleeping right after one slow sensor reports (alternative):** instead of a fixed `report_delay`, you can sleep as soon as the slowest sensor has a value. Set `report_delay` long (say `30s`) and add:

```yaml
sensor:
  - platform: scd4x
    measurement_mode: single_shot
    update_interval: 10s
    co2:
      name: CO2
      on_value:
        then:
          - delay: 2s                      # let the value reach Home Assistant
          - deep_sleep.enter: deep_sleep_1
```

**Trade-offs:**
- **Battery life** is roughly proportional to awake time ÷ total cycle time, because the ESP32-C6 draws tens of milliamps while awake (more while transmitting) and only microamps asleep. Halving the time awake roughly halves the energy per reading; this is why the node sleeps as soon as its readings are sent.
- **A longer `sleep_time`** is the easiest way to extend battery life. 5 minutes suits temperature and humidity; 10–15 minutes is fine for slowly changing values; CO₂ in a busy room may want 2–5 minutes.
- **Updating the firmware:** turn on the stay-awake toggle in Home Assistant first (see [Setting it up in Home Assistant](#setting-it-up-in-home-assistant)), or temporarily raise `report_delay` and `awake_time`.

### Sleep current
While the XIAO sleeps, the board itself draws only a few microamps: the regulator about 2 µA, the protector about 4 µA, the charger's battery leakage about 1 µA and the divider 0.4 µA. The XIAO's own deep-sleep current comes on top; the ESP32-C6 chip alone is rated at 7 µA.

**Measuring it yourself:** power the board from a source meter in place of the cell (for example a Nordic PPK2 in source mode, set to 3.7–4.0 V) and connect to the battery holder's + and − contacts. Unplug USB while measuring, because USB feeds the charger. Remove plug-in sensor boards that have their own power LED or regulator, because they add their own current. On the original board, one tester measured 380 µA asleep with a soil-moisture sensor attached, and 68 mA average (0.6 A peaks while transmitting) during a 3.45 s wake. If you measure far above the figures here, check the plug-in sensors first.

## Repository layout
```
smart_sensor_battery.kicad_*   18350 board (master design)
BMS.kicad_sch                  battery management sub-sheet
Library.pretty/                footprints for all boards (including the universal holder footprint)
3d_models/                     3D models
variants/18650/                18650 board (KiCad project)
variants/21700/                21700 board (KiCad project)
variants/universal/            universal board: 18350, 18650 or 21700 holder (KiCad project)
tools/make_variant.py          generates the variant boards from the master
tools/make_universal.py        generates the universal board from the 21700 variant
tools/make_case.py             generates the 3D-printable case STLs and previews
tools/make_release.py          builds the per-board release zips (python3 tools/make_release.py 1.0)
case/                          3D-printable case: STL files, preview images and print notes
tools/make_gerbers.py          writes Gerber and drill files without KiCad
tools/make_jlc_bom.py          writes JLCPCB BOM and placement files
firmware/                      ESPHome config and secrets template for the XIAO ESP32-C6
homeassistant/                 Home Assistant package (stay-awake toggle)
docs/images/                   board previews used in this README
gerbers/                       JLCPCB-ready Gerber + drill zips for all four boards
assembly/                      JLCPCB BOM and placement (CPL) files for all four boards
```

## Changing the design
The root (18350) project is the master. Make circuit or layout changes there, then regenerate the larger boards so they pick up the change (Python 3, no extra packages):

```
python3 tools/make_variant.py --name 18650 \
    --footprint Library.pretty/BatteryHolder_Keystone_1042_1x18650.kicad_mod \
    --value 1042 --mpn "Keystone 1042" --neg-y 108.08 --set R1=910

python3 tools/make_variant.py --name 21700 \
    --footprint Library.pretty/BatteryHolder_Keystone_1121_1x21700.kicad_mod \
    --value 1121 --mpn "Keystone 1121" --cell 21700 --set R1=910
python3 tools/make_universal.py   # universal board, built from variants/21700
```

The script swaps the holder, resizes the outline, extends the battery traces, stretches the ground pours and updates BT1 in the schematic. `--set REF=VALUE` overrides a part value in that variant; the larger cells use it to raise the charge current. It also reports any holder hole that would land on existing copper; use `--neg-y` to slide the holder along the board if one does. To add another cell size, point `--footprint` at that holder's KiCad footprint.

The 18650 footprint comes from the official KiCad library (CC-BY-SA 4.0 with the KiCad library exception), with its pads renamed P/N to match the BT1 symbol.

## ⚠️ Safety Warning
This board involves **Lithium-Ion battery charging**. 
*   This is an **experimental prototype** from a hobbyist. **I am not a professional engineer**. It has **not** been certified by safety agencies (UL, CE, etc.).
*   Lithium batteries can be dangerous if mishandled (risk of thermal runaway, fire, explosion, and serious injury).
*   **DO NOT leave this device unattended with a battery connected**
*   By using these files, you agree that you are solely responsible for verifying the safety of the circuit.

## License & Liability

### 1. Non-Commercial Use Only
This project is shared under the [Creative Commons Attribution-NonCommercial-ShareAlike 4.0 International](https://creativecommons.org/licenses/by-nc-sa/4.0/) license.
*  **You are free to:** Download, modify, and build this for personal use or learning.
*  **You may NOT:** Sell this board, use it in a product you sell, or use these files for any commercial purpose.
*  If you modify and share this design, you must share it under this same license.

### 2. No Liability (Disclaimer)
These files are provided "As Is" for educational purposes ONLY. I am sharing my personal project notes. **I accept no liability for any damage, injury, or loss** that occurs from the use or assembly of these files. Use them at your own risk.

## Credits
Original design, schematic, layout and video by [FeatureNAB](https://github.com/FeatureNAB/smart-sensor-battery-pack). This fork's changes are listed under [Changes from the original design](#changes-from-the-original-design) and are shared under the same CC BY-NC-SA 4.0 license, as the original requires.

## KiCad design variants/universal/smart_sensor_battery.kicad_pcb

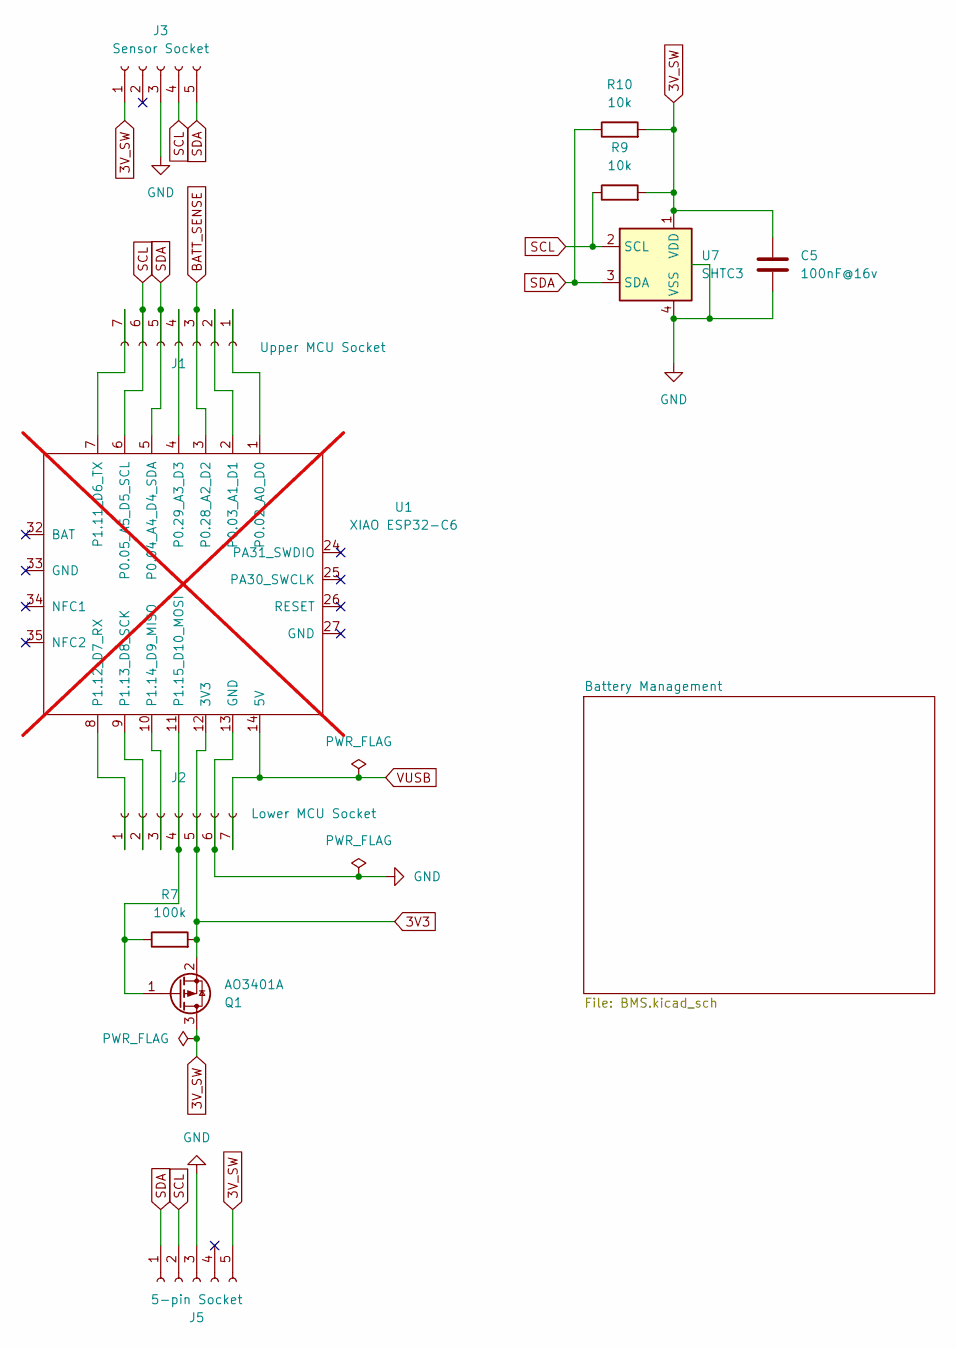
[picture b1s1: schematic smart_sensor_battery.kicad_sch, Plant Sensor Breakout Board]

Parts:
C5: 100nF@16v; C_0402_1005Metric; LCSC Part no. C1525
J1: Upper MCU Socket; PinSocket_1x07_P2.54mm_Vertical_SMD_Pin1Left; LCSC Part no. C42379199
J2: Lower MCU Socket; PinSocket_1x07_P2.54mm_Vertical_SMD_Pin1Right; LCSC Part no. C42379199
J3: Sensor Socket; PinSocket_1x07_P2.54mm_Vertical_SMD_Pin1Right; LCSC Part no. C42379199
J5: 5-pin Socket; PinSocket_1x05_P2.54mm_Vertical_SMD_Pin1Left; LCSC Part no. C42379198
Q1: AO3401A; SOT-23; LCSC Part no. C15127
R7: 100k; R_0402_1005Metric; LCSC Part no. C25741
R9, R10: 10k; R_0402_1005Metric; LCSC Part no. C25744
U1: XIAO ESP32-C6; XIAO-nRF52840-SMD; not fitted
U7: SHTC3; Sensirion_DFN-4-1EP_2x2mm_P1mm_EP0.7x1.6mm; LCSC Part no. C194656

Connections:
3V3: J2.5, Q1.2 (S), R7.2, U1.12 (3V3); also elsewhere on the board
3V_SW: C5.1, J3.1, J5.5, Q1.3 (D), R9.2, R10.2, U7.1 (VDD)
BATT_SENSE: J1.3, U1.3 (P0.28_A2_D2); also elsewhere on the board
GND: C5.2, J2.6, J3.3, J5.3, U1.13 (GND), U7.4 (VSS), U7.5 (GND_(centre_pad)); also elsewhere on the board
unnamed: J1.1, U1.1 (P0.02_A0_D0)
unnamed: J1.2, U1.2 (P0.03_A1_D1)
unnamed: J1.4, U1.4 (P0.29_A3_D3)
unnamed: J1.7, U1.7 (P1.11_D6_TX)
unnamed: J2.1, U1.8 (P1.12_D7_RX)
unnamed: J2.2, U1.9 (P1.13_D8_SCK)
unnamed: J2.3, U1.10 (P1.14_D9_MISO)
unnamed: J2.4, Q1.1 (G), R7.1, U1.11 (P1.15_D10_MOSI)
SCL: J1.6, J3.4, J5.2, R9.1, U1.6 (P0.05_A5_D5_SCL), U7.2 (SCL)
SDA: J1.5, J3.5, J5.1, R10.1, U1.5 (P0.04_A4_D4_SDA), U7.3 (SDA)
VUSB: J2.7, U1.14 (5V); also elsewhere on the board

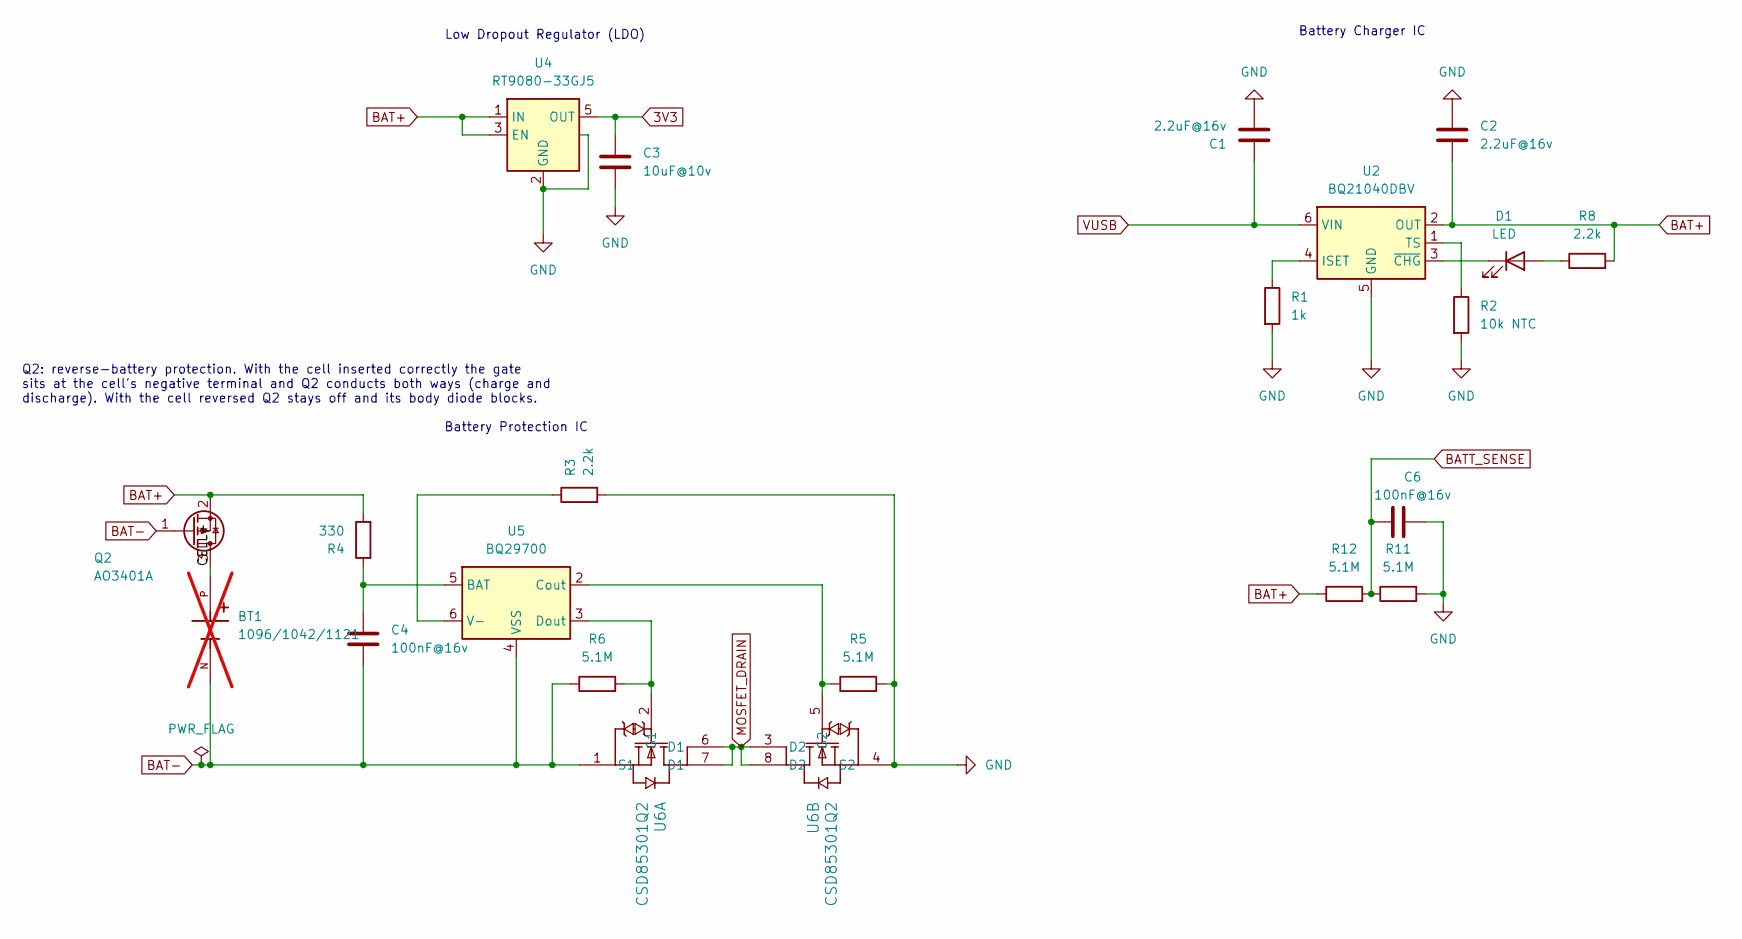
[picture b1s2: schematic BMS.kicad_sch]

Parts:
BT1: 1096/1042/1121; BatteryHolder_Universal_18350_18650_21700; PARTREV A; not fitted
C1, C2: 2.2uF@16v; C_0603_1608Metric; LCSC Part no. C23630
C3: 10uF@10v; C_0603_1608Metric; LCSC Part no. C19702
C4, C6: 100nF@16v; C_0402_1005Metric; LCSC Part no. C1525
D1: LED; LED_0402_1005Metric; LCSC Part no. C74339
Q2: AO3401A; SOT-23; LCSC Part no. C15127
R1: 1k; R_0402_1005Metric; LCSC Part no. C11702
R2: 10k NTC; R_0402_1005Metric; MPN Murata NCP15XH103F03RC; LCSC Part no. C77131
R3, R8: 2.2k; R_0402_1005Metric; LCSC Part no. C25879
R4: 330; R_0402_1005Metric; LCSC Part no. C25104
R5, R6, R11, R12: 5.1M; R_0402_1005Metric; LCSC Part no. C26092
U2: BQ21040DBV; SOT-23-6; LCSC Part no. C202311
U4: RT9080-33GJ5; SOT-23-5; MPN Richtek RT9080-33GJ5; LCSC Part no. C841192
U5: BQ29700; WSON-6_1.5x1.5mm_P0.5mm; LCSC Part no. C183096
U6: CSD85301Q2; LCSC Part no. C544396

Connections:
3V3: C3.1, U4.5 (OUT); also elsewhere on the board
BAT+: C2.1, Q2.2 (S), R4.2, R8.2, R12.1, U2.2 (OUT), U4.1 (IN), U4.3 (EN)
BAT-: BT1.N, C4.2, Q2.1 (G), R6.1, U5.4 (VSS), U6.1 (S1)
BATT_SENSE: C6.1, R11.1, R12.2; also elsewhere on the board
CELL+: BT1.P, Q2.3 (D)
GND: C1.2, C2.2, C3.2, C6.2, R1.2, R2.2, R3.2, R5.2, R11.2, U2.5 (GND), U4.2 (GND), U4.4 (NC_(GND)), U6.4 (S2); also elsewhere on the board
MOSFET_DRAIN: U6.3 (D2), U6.6 (D1), U6.7 (D1), U6.8 (D2)
unnamed: D1.2 (A), R8.1
unnamed: D1.1 (K), U2.3 (~CHG)
unnamed: R1.1, U2.4 (ISET)
unnamed: R2.1, U2.1 (TS)
unnamed: C4.1, R4.1, U5.5 (BAT)
unnamed: R5.1, U5.2 (Cout), U6.5 (G2)
unnamed: R6.2, U5.3 (Dout), U6.2 (G1)
unnamed: R3.1, U5.6 (V-)
VUSB: C1.1, U2.6 (VIN); also elsewhere on the board

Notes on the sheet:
Battery Protection IC
Battery Charger IC
Low Dropout Regulator (LDO)
Q2: reverse-battery protection. With the cell inserted correctly the gate sits at the cell's negative terminal and Q2 conducts both ways (charge and discharge). With the cell reversed Q2 stays off and its body diode blocks.

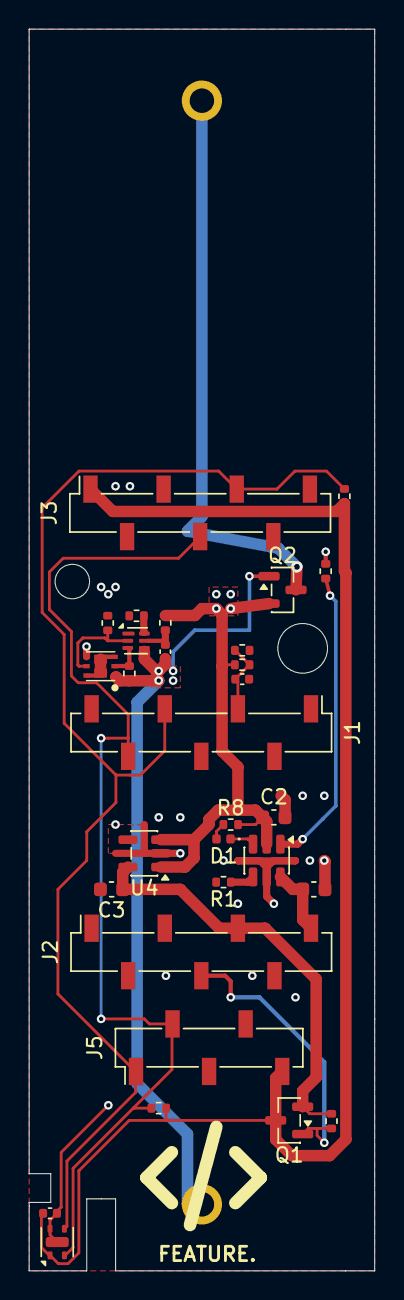
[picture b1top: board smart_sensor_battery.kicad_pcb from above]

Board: 2 copper layers, 24.0 x 86.2 mm, 31 parts (1 on the bottom side), 20 nets.

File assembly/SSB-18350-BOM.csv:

Comment,Designator,Footprint,LCSC Part #
2.2uF@16v,"C1,C2",C_0603_1608Metric,C23630
10uF@10v,C3,C_0603_1608Metric,C19702
100nF@16v,"C4,C5,C6",C_0402_1005Metric,C1525
LED,D1,LED_0402_1005Metric,C74339
Upper MCU Socket,J1,PinSocket_1x07_P2.54mm_Vertical_SMD_Pin1Left,C42379199
Lower MCU Socket,J2,PinSocket_1x07_P2.54mm_Vertical_SMD_Pin1Right,C42379199
Sensor Socket,J3,PinSocket_1x07_P2.54mm_Vertical_SMD_Pin1Right,C42379199
5-pin Socket,J5,PinSocket_1x05_P2.54mm_Vertical_SMD_Pin1Left,C42379198
AO3401A,"Q1,Q2",SOT-23,C15127
1.2k,R1,R_0402_1005Metric,C25862
10k NTC,R2,R_0402_1005Metric,C77131
2.2k,"R3,R8",R_0402_1005Metric,C25879
330,R4,R_0402_1005Metric,C25104
5.1M,"R5,R6,R11,R12",R_0402_1005Metric,C26092
100k,R7,R_0402_1005Metric,C25530
10k,"R9,R10",R_0402_1005Metric,C25744
BQ21040DBV,U2,SOT-23-6,C202311
RT9080-33GJ5,U4,SOT-23-5,C841192
BQ29700,U5,WSON-6_1.5x1.5mm_P0.5mm,C183096
CSD85301Q2,U6,CSD85301Q2,C544396
SHTC3,U7,Sensirion_DFN-4-1EP_2x2mm_P1mm_EP0.7x1.6mm,C194656
